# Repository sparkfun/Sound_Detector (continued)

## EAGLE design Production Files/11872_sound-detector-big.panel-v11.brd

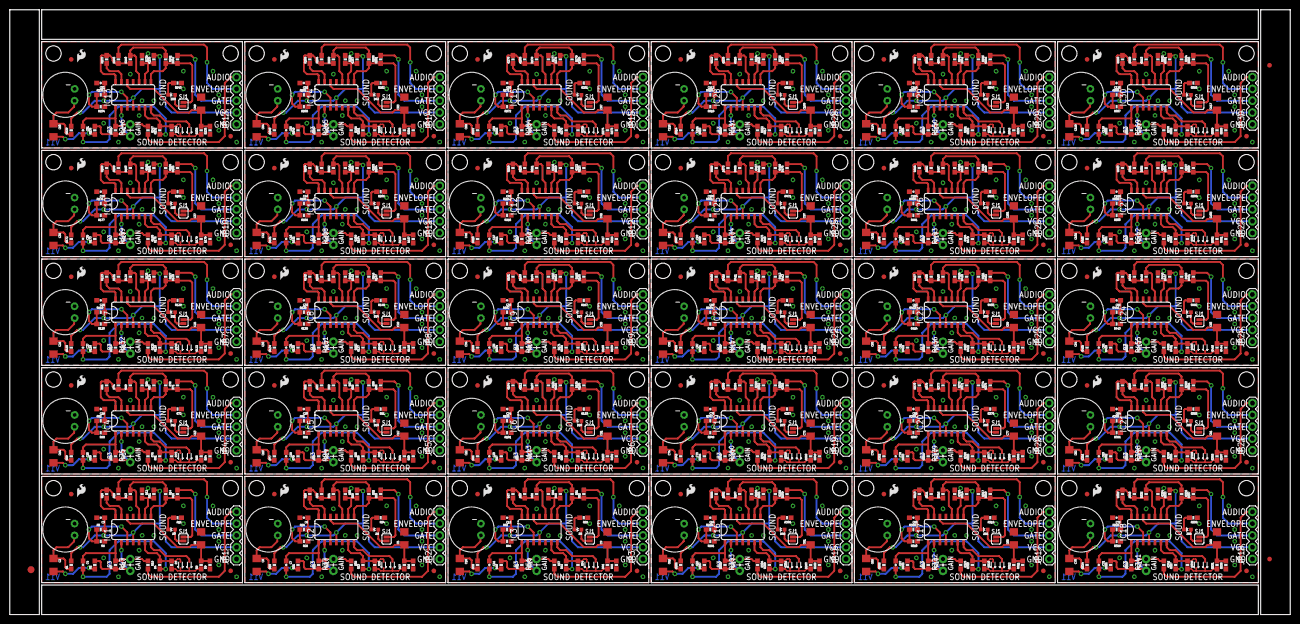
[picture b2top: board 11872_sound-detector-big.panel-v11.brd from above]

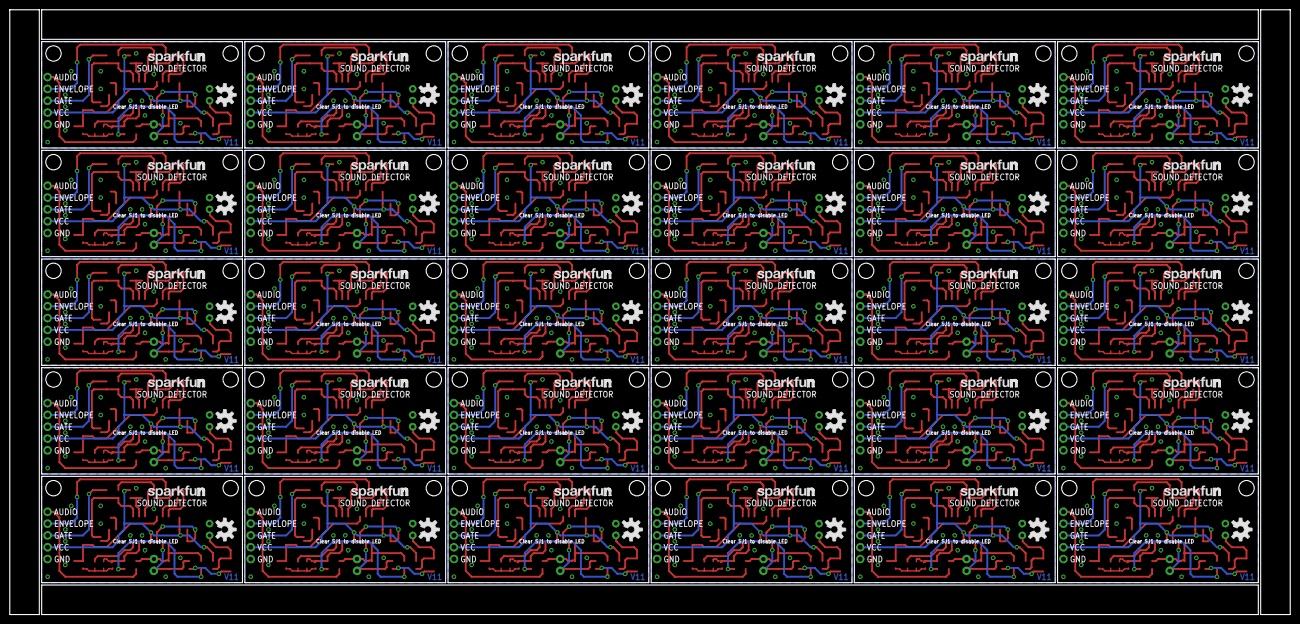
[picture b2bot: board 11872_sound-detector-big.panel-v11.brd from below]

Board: 2 copper layers, 275.3 x 130.0 mm, 1113 parts (60 on the bottom side), 660 nets.

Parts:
C1, C2, C5, C6, C9, C10, C13, C14, C17, C18, C21, C22, C25, C26, C29, C30, C33, C34, C37, C38, C41, C42, C45, C46, C49, C50, C53, C54, C57, C58, C61, C62, C65, C66, C69, C70, C73, C74, C77, C78, C81, C82, C85, C86, C89, C90, C93, C94, C97, C98, C101, C102, C105, C106, C109, C110, C113, C114, C117, C118: 10uF; 1206
C3, C4, C7, C8, C11, C12, C15, C16, C19, C20, C23, C24, C27, C28, C31, C32, C35, C36, C39, C40, C43, C44, C47, C48, C51, C52, C55, C56, C59, C60, C63, C64, C67, C68, C71, C72, C75, C76, C79, C80, C83, C84, C87, C88, C91, C92, C95, C96, C99, C100, C103, C104, C107, C108, C111, C112, C115, C116, C119, C120: 1.0uF; 0603-CAP
D1, D2, D4, D5, D7, D8, D10, D11, D13, D14, D16, D17, D19, D20, D22, D23, D25, D26, D28, D29, D31, D32, D34, D35, D37, D38, D40, D41, D43, D44, D46, D47, D49, D50, D52, D53, D55, D56, D58, D59, D61, D62, D64, D65, D67, D68, D70, D71, D73, D74, D76, D77, D79, D80, D82, D83, D85, D86, D88, D89: RB751; SOD-523
D3, D6, D9, D12, D15, D18, D21, D24, D27, D30, D33, D36, D39, D42, D45, D48, D51, D54, D57, D60, D63, D66, D69, D72, D75, D78, D81, D84, D87, D90: RED; LED-0603
E$1: FIDUCIAL-1.5X3
E$4, E$6: FIDUCIAL-1X2
FID1, FID2, FID3, FID4, FID5, FID6, FID7, FID8, FID9, FID10, FID11, FID12, FID13, FID14, FID15, FID16, FID17, FID18, FID19, FID20, FID21, FID22, FID23, FID24, FID25, FID26, FID27, FID28, FID29, FID30, FID31, FID32, FID33, FID34, FID35, FID36, FID37, FID38, FID39, FID40, FID41, FID42, FID43, FID44, FID45, FID46, FID47, FID48, FID49, FID50, FID51, FID52, FID53, FID54, FID55, FID56, FID57, FID58, FID59, FID60: FIDUCIAL1X2; FIDUCIAL-1X2
IC1, IC2, IC3, IC4, IC5, IC6, IC7, IC8, IC9, IC10, IC11, IC12, IC13, IC14, IC15, IC16, IC17, IC18, IC19, IC20, IC21, IC22, IC23, IC24, IC25, IC26, IC27, IC28, IC29, IC30: LMV324; SO014
JP1, JP2, JP3, JP4, JP5, JP6, JP7, JP8, JP9, JP10, JP11, JP12, JP13, JP14, JP15, JP16, JP17, JP18, JP19, JP20, JP21, JP22, JP23, JP24, JP25, JP26, JP27, JP28, JP29, JP30: IO Connector; 1X05
LOGO1, LOGO4, LOGO7, LOGO10, LOGO13, LOGO16, LOGO19, LOGO22, LOGO25, LOGO28, LOGO31, LOGO34, LOGO37, LOGO40, LOGO43, LOGO46, LOGO49, LOGO52, LOGO55, LOGO58, LOGO61, LOGO64, LOGO67, LOGO70, LOGO73, LOGO76, LOGO79, LOGO82, LOGO85, LOGO88: OSHW-LOGOM; OSHW-LOGO-M
LOGO2, LOGO5, LOGO8, LOGO11, LOGO14, LOGO17, LOGO20, LOGO23, LOGO26, LOGO29, LOGO32, LOGO35, LOGO38, LOGO41, LOGO44, LOGO47, LOGO50, LOGO53, LOGO56, LOGO59, LOGO62, LOGO65, LOGO68, LOGO71, LOGO74, LOGO77, LOGO80, LOGO83, LOGO86, LOGO89: LOGO-SFENW2; SFE-NEW-WEB
LOGO3, LOGO6, LOGO9, LOGO12, LOGO15, LOGO18, LOGO21, LOGO24, LOGO27, LOGO30, LOGO33, LOGO36, LOGO39, LOGO42, LOGO45, LOGO48, LOGO51, LOGO54, LOGO57, LOGO60, LOGO63, LOGO66, LOGO69, LOGO72, LOGO75, LOGO78, LOGO81, LOGO84, LOGO87, LOGO90: LOGO-SFESK; SFE-LOGO-FLAME
MIC1, MIC2, MIC3, MIC4, MIC5, MIC6, MIC7, MIC8, MIC9, MIC10, MIC11, MIC12, MIC13, MIC14, MIC15, MIC16, MIC17, MIC18, MIC19, MIC20, MIC21, MIC22, MIC23, MIC24, MIC25, MIC26, MIC27, MIC28, MIC29, MIC30: MIC9.7MM; MIC-9.7MM
R1, R16, R20, R34, R39, R53, R58, R72, R77, R91, R96, R110, R115, R129, R134, R148, R153, R167, R172, R186, R191, R205, R210, R224, R229, R243, R248, R262, R267, R281, R286, R300, R305, R319, R324, R338, R343, R357, R362, R376, R381, R395, R400, R414, R419, R433, R438, R452, R457, R471, R476, R490, R495, R509, R514, R528, R533, R547, R552, R566: 2.2k; 0603-RES
R2, R10, R13, R21, R28, R31, R40, R47, R50, R59, R66, R69, R78, R85, R88, R97, R104, R107, R116, R123, R126, R135, R142, R145, R154, R161, R164, R173, R180, R183, R192, R199, R202, R211, R218, R221, R230, R237, R240, R249, R256, R259, R268, R275, R278, R287, R294, R297, R306, R313, R316, R325, R332, R335, R344, R351, R354, R363, R370, R373, R382, R389, R392, R401, R408, R411, R420, R427, R430, R439, R446, R449, R458, R465, R468, R477, R484, R487, R496, R503, R506, R515, R522, R525, R534, R541, R544, R553, R560, R563: 1K; 0603-RES
R3, R11, R14, R22, R29, R32, R41, R48, R51, R60, R67, R70, R79, R86, R89, R98, R105, R108, R117, R124, R127, R136, R143, R146, R155, R162, R165, R174, R181, R184, R193, R200, R203, R212, R219, R222, R231, R238, R241, R250, R257, R260, R269, R276, R279, R288, R295, R298, R307, R314, R317, R326, R333, R336, R345, R352, R355, R364, R371, R374, R383, R390, R393, R402, R409, R412, R421, R428, R431, R440, R447, R450, R459, R466, R469, R478, R485, R488, R497, R504, R507, R516, R523, R526, R535, R542, R545, R554, R561, R564: 100k; 0603-RES
R4, R5, R6, R9, R23, R24, R25, R26, R42, R43, R44, R45, R61, R62, R63, R64, R80, R81, R82, R83, R99, R100, R101, R102, R118, R119, R120, R121, R137, R138, R139, R140, R156, R157, R158, R159, R175, R176, R177, R178, R194, R195, R196, R197, R213, R214, R215, R216, R232, R233, R234, R235, R251, R252, R253, R254, R270, R271, R272, R273, R289, R290, R291, R292, R308, R309, R310, R311, R327, R328, R329, R330, R346, R347, R348, R349, R365, R366, R367, R368, R384, R385, R386, R387, R403, R404, R405, R406, R422, R423, R424, R425, R441, R442, R443, R444, R460, R461, R462, R463, R479, R480, R481, R482, R498, R499, R500, R501, R517, R518, R519, R520, R536, R537, R538, R539, R555, R556, R557, R558: 10K; 0603-RES
R7, R35, R54, R73, R92, R111, R130, R149, R168, R187, R206, R225, R244, R263, R282, R301, R320, R339, R358, R377, R396, R415, R434, R453, R472, R491, R510, R529, R548, R567: 22K; 0603-RES
R8, R15, R18, R19, R27, R33, R36, R38, R46, R52, R55, R57, R65, R71, R74, R76, R84, R90, R93, R95, R103, R109, R112, R114, R122, R128, R131, R133, R141, R147, R150, R152, R160, R166, R169, R171, R179, R185, R188, R190, R198, R204, R207, R209, R217, R223, R226, R228, R236, R242, R245, R247, R255, R261, R264, R266, R274, R280, R283, R285, R293, R299, R302, R304, R312, R318, R321, R323, R331, R337, R340, R342, R350, R356, R359, R361, R369, R375, R378, R380, R388, R394, R397, R399, R407, R413, R416, R418, R426, R432, R435, R437, R445, R451, R454, R456, R464, R470, R473, R475, R483, R489, R492, R494, R502, R508, R511, R513, R521, R527, R530, R532, R540, R546, R549, R551, R559, R565, R568, R570: 100; 0603-RES
R12, R30, R49, R68, R87, R106, R125, R144, R163, R182, R201, R220, R239, R258, R277, R296, R315, R334, R353, R372, R391, R410, R429, R448, R467, R486, R505, R524, R543, R562: 3.3k; 0603-RES
R17, R37, R56, R75, R94, R113, R132, R151, R170, R189, R208, R227, R246, R265, R284, R303, R322, R341, R360, R379, R398, R417, R436, R455, R474, R493, R512, R531, R550, R569: GAIN; AXIAL-0.1EZ
SJ1, SJ2, SJ3, SJ4, SJ5, SJ6, SJ7, SJ8, SJ9, SJ10, SJ11, SJ12, SJ13, SJ14, SJ15, SJ16, SJ17, SJ18, SJ19, SJ20, SJ21, SJ22, SJ23, SJ24, SJ25, SJ26, SJ27, SJ28, SJ29, SJ30: Disable LED; SJ_2S
STANDOFF1, STANDOFF2, STANDOFF3, STANDOFF4, STANDOFF5, STANDOFF6, STANDOFF7, STANDOFF8, STANDOFF9, STANDOFF10, STANDOFF11, STANDOFF12, STANDOFF13, STANDOFF14, STANDOFF15, STANDOFF16, STANDOFF17, STANDOFF18, STANDOFF19, STANDOFF20, STANDOFF21, STANDOFF22, STANDOFF23, STANDOFF24, STANDOFF25, STANDOFF26, STANDOFF27, STANDOFF28, STANDOFF29, STANDOFF30, STANDOFF31, STANDOFF32, STANDOFF33, STANDOFF34, STANDOFF35, STANDOFF36, STANDOFF37, STANDOFF38, STANDOFF39, STANDOFF40, STANDOFF41, STANDOFF42, STANDOFF43, STANDOFF44, STANDOFF45, STANDOFF46, STANDOFF47, STANDOFF48, STANDOFF49, STANDOFF50, STANDOFF51, STANDOFF52, STANDOFF53, STANDOFF54, STANDOFF55, STANDOFF56, STANDOFF57, STANDOFF58, STANDOFF59, STANDOFF60: STAND-OFF

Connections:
AMPENV: IC1.14, R10.2, R13.1, R18.1
AMPENV1: IC2.14, R28.2, R31.1, R36.1
AMPENV2: IC3.14, R47.2, R50.1, R55.1
AMPENV3: IC4.14, R66.2, R69.1, R74.1
AMPENV4: IC5.14, R85.2, R88.1, R93.1
AMPENV5: IC6.14, R104.2, R107.1, R112.1
AMPENV6: IC7.14, R123.2, R126.1, R131.1
AMPENV7: IC8.14, R142.2, R145.1, R150.1
AMPENV8: IC9.14, R161.2, R164.1, R169.1
AMPENV9: IC10.14, R180.2, R183.1, R188.1
AMPENV10: IC11.14, R199.2, R202.1, R207.1
AMPENV11: IC12.14, R218.2, R221.1, R226.1
AMPENV12: IC13.14, R237.2, R240.1, R245.1
AMPENV13: IC14.14, R256.2, R259.1, R264.1
AMPENV14: IC15.14, R275.2, R278.1, R283.1
AMPENV15: IC16.14, R294.2, R297.1, R302.1
AMPENV16: IC17.14, R313.2, R316.1, R321.1
AMPENV17: IC18.14, R332.2, R335.1, R340.1
AMPENV18: IC19.14, R351.2, R354.1, R359.1
AMPENV19: IC20.14, R370.2, R373.1, R378.1
AMPENV20: IC21.14, R389.2, R392.1, R397.1
AMPENV21: IC22.14, R408.2, R411.1, R416.1
AMPENV22: IC23.14, R427.2, R430.1, R435.1
AMPENV23: IC24.14, R446.2, R449.1, R454.1
AMPENV24: IC25.14, R465.2, R468.1, R473.1
AMPENV25: IC26.14, R484.2, R487.1, R492.1
AMPENV26: IC27.14, R503.2, R506.1, R511.1
AMPENV27: IC28.14, R522.2, R525.1, R530.1
AMPENV28: IC29.14, R541.2, R544.1, R549.1
AMPENV29: IC30.14, R560.2, R563.1, R568.1
AUDIO: JP1.5, R19.2
AUDIO1: JP2.5, R38.2
AUDIO2: JP3.5, R57.2
AUDIO3: JP4.5, R76.2
AUDIO4: JP5.5, R95.2
AUDIO5: JP6.5, R114.2
AUDIO6: JP7.5, R133.2
AUDIO7: JP8.5, R152.2
AUDIO8: JP9.5, R171.2
AUDIO9: JP10.5, R190.2
AUDIO10: JP11.5, R209.2
AUDIO11: JP12.5, R228.2
AUDIO12: JP13.5, R247.2
AUDIO13: JP14.5, R266.2
AUDIO14: JP15.5, R285.2
AUDIO15: JP16.5, R304.2
AUDIO16: JP17.5, R323.2
AUDIO17: JP18.5, R342.2
AUDIO18: JP19.5, R361.2
AUDIO19: JP20.5, R380.2
AUDIO20: JP21.5, R399.2
AUDIO21: JP22.5, R418.2
AUDIO22: JP23.5, R437.2
AUDIO23: JP24.5, R456.2
AUDIO24: JP25.5, R475.2
AUDIO25: JP26.5, R494.2
AUDIO26: JP27.5, R513.2
AUDIO27: JP28.5, R532.2
AUDIO28: JP29.5, R551.2
AUDIO29: JP30.5, R570.2
ENVELOPE: JP1.4, R18.2
ENVELOPE1: JP2.4, R36.2
ENVELOPE2: JP3.4, R55.2
ENVELOPE3: JP4.4, R74.2
ENVELOPE4: JP5.4, R93.2
ENVELOPE5: JP6.4, R112.2
ENVELOPE6: JP7.4, R131.2
ENVELOPE7: JP8.4, R150.2
ENVELOPE8: JP9.4, R169.2
ENVELOPE9: JP10.4, R188.2
ENVELOPE10: JP11.4, R207.2
ENVELOPE11: JP12.4, R226.2
ENVELOPE12: JP13.4, R245.2
ENVELOPE13: JP14.4, R264.2
ENVELOPE14: JP15.4, R283.2
ENVELOPE15: JP16.4, R302.2
ENVELOPE16: JP17.4, R321.2
ENVELOPE17: JP18.4, R340.2
ENVELOPE18: JP19.4, R359.2
ENVELOPE19: JP20.4, R378.2
ENVELOPE20: JP21.4, R397.2
ENVELOPE21: JP22.4, R416.2
ENVELOPE22: JP23.4, R435.2
ENVELOPE23: JP24.4, R454.2
ENVELOPE24: JP25.4, R473.2
ENVELOPE25: JP26.4, R492.2
ENVELOPE26: JP27.4, R511.2
ENVELOPE27: JP28.4, R530.2
ENVELOPE28: JP29.4, R549.2
ENVELOPE29: JP30.4, R568.2
GATE: JP1.3, R15.2
GATE1: JP2.3, R33.2
GATE2: JP3.3, R52.2
GATE3: JP4.3, R71.2
GATE4: JP5.3, R90.2
GATE5: JP6.3, R109.2
GATE6: JP7.3, R128.2
GATE7: JP8.3, R147.2
GATE8: JP9.3, R166.2
GATE9: JP10.3, R185.2
GATE10: JP11.3, R204.2
GATE11: JP12.3, R223.2
GATE12: JP13.3, R242.2
GATE13: JP14.3, R261.2
GATE14: JP15.3, R280.2
GATE15: JP16.3, R299.2
GATE16: JP17.3, R318.2
GATE17: JP18.3, R337.2
GATE18: JP19.3, R356.2
GATE19: JP20.3, R375.2
GATE20: JP21.3, R394.2
GATE21: JP22.3, R413.2
GATE22: JP23.3, R432.2
GATE23: JP24.3, R451.2
GATE24: JP25.3, R470.2
GATE25: JP26.3, R489.2
GATE26: JP27.3, R508.2
GATE27: JP28.3, R527.2
GATE28: JP29.3, R546.2
GATE29: JP30.3, R565.2
GND: C1.2, C3.2, IC1.5, IC1.11, JP1.1, MIC1.2, R6.1, R9.1, R12.1, R16.1
GND1: C5.2, C8.2, IC2.5, IC2.11, JP2.1, MIC2.2, R25.1, R26.1, R30.1, R34.1
GND2: C9.2, C12.2, IC3.5, IC3.11, JP3.1, MIC3.2, R44.1, R45.1, R49.1, R53.1
GND3: C13.2, C16.2, IC4.5, IC4.11, JP4.1, MIC4.2, R63.1, R64.1, R68.1, R72.1
GND4: C17.2, C20.2, IC5.5, IC5.11, JP5.1, MIC5.2, R82.1, R83.1, R87.1, R91.1
GND5: C21.2, C24.2, IC6.5, IC6.11, JP6.1, MIC6.2, R101.1, R102.1, R106.1, R110.1
GND6: C25.2, C28.2, IC7.5, IC7.11, JP7.1, MIC7.2, R120.1, R121.1, R125.1, R129.1
GND7: C29.2, C32.2, IC8.5, IC8.11, JP8.1, MIC8.2, R139.1, R140.1, R144.1, R148.1
GND8: C33.2, C36.2, IC9.5, IC9.11, JP9.1, MIC9.2, R158.1, R159.1, R163.1, R167.1
GND9: C37.2, C40.2, IC10.5, IC10.11, JP10.1, MIC10.2, R177.1, R178.1, R182.1, R186.1
GND10: C41.2, C44.2, IC11.5, IC11.11, JP11.1, MIC11.2, R196.1, R197.1, R201.1, R205.1
GND11: C45.2, C48.2, IC12.5, IC12.11, JP12.1, MIC12.2, R215.1, R216.1, R220.1, R224.1
GND12: C49.2, C52.2, IC13.5, IC13.11, JP13.1, MIC13.2, R234.1, R235.1, R239.1, R243.1
GND13: C53.2, C56.2, IC14.5, IC14.11, JP14.1, MIC14.2, R253.1, R254.1, R258.1, R262.1
GND14: C57.2, C60.2, IC15.5, IC15.11, JP15.1, MIC15.2, R272.1, R273.1, R277.1, R281.1
GND15: C61.2, C64.2, IC16.5, IC16.11, JP16.1, MIC16.2, R291.1, R292.1, R296.1, R300.1
GND16: C65.2, C68.2, IC17.5, IC17.11, JP17.1, MIC17.2, R310.1, R311.1, R315.1, R319.1
GND17: C69.2, C72.2, IC18.5, IC18.11, JP18.1, MIC18.2, R329.1, R330.1, R334.1, R338.1
GND18: C73.2, C76.2, IC19.5, IC19.11, JP19.1, MIC19.2, R348.1, R349.1, R353.1, R357.1
GND19: C77.2, C80.2, IC20.5, IC20.11, JP20.1, MIC20.2, R367.1, R368.1, R372.1, R376.1
GND20: C81.2, C84.2, IC21.5, IC21.11, JP21.1, MIC21.2, R386.1, R387.1, R391.1, R395.1
GND21: C85.2, C88.2, IC22.5, IC22.11, JP22.1, MIC22.2, R405.1, R406.1, R410.1, R414.1
GND22: C89.2, C92.2, IC23.5, IC23.11, JP23.1, MIC23.2, R424.1, R425.1, R429.1, R433.1
GND23: C93.2, C96.2, IC24.5, IC24.11, JP24.1, MIC24.2, R443.1, R444.1, R448.1, R452.1
GND24: C97.2, C100.2, IC25.5, IC25.11, JP25.1, MIC25.2, R462.1, R463.1, R467.1, R471.1
GND25: C101.2, C104.2, IC26.5, IC26.11, JP26.1, MIC26.2, R481.1, R482.1, R486.1, R490.1
GND26: C105.2, C108.2, IC27.5, IC27.11, JP27.1, MIC27.2, R500.1, R501.1, R505.1, R509.1
GND27: C109.2, C112.2, IC28.5, IC28.11, JP28.1, MIC28.2, R519.1, R520.1, R524.1, R528.1
GND28: C113.2, C116.2, IC29.5, IC29.11, JP29.1, MIC29.2, R538.1, R539.1, R543.1, R547.1
GND29: C117.2, C120.2, IC30.5, IC30.11, JP30.1, MIC30.2, R557.1, R558.1, R562.1, R566.1
N$: C4.1, IC1.1, R3.2, R17.P$2, R19.1
unnamed: C2.1, MIC1.1, R1.1
unnamed: IC1.3, R5.1, R6.2
unnamed: D3.C, R16.2
unnamed: IC1.2, R2.2, R3.1, R17.P$1
unnamed: C2.2, R2.1
unnamed: C4.2, R4.1
unnamed: D1.A, IC1.6, R4.2, R7.1
unnamed: D2.A, IC1.7
unnamed: D1.C, D2.C, R7.2, R8.1
unnamed: C1.1, IC1.12, R8.2, R9.2
unnamed: IC1.13, R10.1
unnamed: D3.A, SJ1.1
unnamed: C6.1, MIC2.1, R20.1
unnamed: IC2.3, R24.1, R25.2
unnamed: IC1.9, R11.1, R12.2
unnamed: IC1.10, R13.2, R14.1
unnamed: IC1.8, R14.2, R15.1, SJ1.2
unnamed: IC2.2, R21.2, R22.1, R37.P$1
unnamed: C6.2, R21.1
unnamed: C7.2, R23.1
unnamed: D4.A, IC2.6, R23.2, R35.1
unnamed: D5.A, IC2.7
unnamed: D4.C, D5.C, R27.1, R35.2
unnamed: C5.1, IC2.12, R26.2, R27.2
unnamed: IC2.13, R28.1
unnamed: IC2.9, R29.1, R30.2
unnamed: IC2.10, R31.2, R32.1
unnamed: IC2.8, R32.2, R33.1, SJ2.2
unnamed: D6.C, R34.2
unnamed: D6.A, SJ2.1
unnamed: C7.1, IC2.1, R22.2, R37.P$2, R38.1
unnamed: C10.1, MIC3.1, R39.1
unnamed: IC3.3, R43.1, R44.2
unnamed: IC3.2, R40.2, R41.1, R56.P$1
unnamed: C10.2, R40.1
unnamed: C11.2, R42.1
unnamed: D7.A, IC3.6, R42.2, R54.1
unnamed: D8.A, IC3.7
unnamed: D7.C, D8.C, R46.1, R54.2
unnamed: C9.1, IC3.12, R45.2, R46.2
unnamed: IC3.13, R47.1
unnamed: IC3.9, R48.1, R49.2
unnamed: IC3.10, R50.2, R51.1
unnamed: IC3.8, R51.2, R52.1, SJ3.2
unnamed: D9.C, R53.2
unnamed: D9.A, SJ3.1
unnamed: C11.1, IC3.1, R41.2, R56.P$2, R57.1
unnamed: C14.1, MIC4.1, R58.1
unnamed: IC4.3, R62.1, R63.2
unnamed: IC4.2, R59.2, R60.1, R75.P$1
unnamed: C14.2, R59.1
unnamed: C15.2, R61.1
unnamed: D10.A, IC4.6, R61.2, R73.1
unnamed: D11.A, IC4.7
unnamed: D10.C, D11.C, R65.1, R73.2
unnamed: C13.1, IC4.12, R64.2, R65.2
unnamed: IC4.13, R66.1
unnamed: IC4.9, R67.1, R68.2
unnamed: IC4.10, R69.2, R70.1
unnamed: IC4.8, R70.2, R71.1, SJ4.2
unnamed: D12.C, R72.2
unnamed: D12.A, SJ4.1
unnamed: C15.1, IC4.1, R60.2, R75.P$2, R76.1
unnamed: C18.1, MIC5.1, R77.1
unnamed: IC5.3, R81.1, R82.2
unnamed: IC5.2, R78.2, R79.1, R94.P$1
unnamed: C18.2, R78.1
unnamed: C19.2, R80.1
unnamed: D13.A, IC5.6, R80.2, R92.1
unnamed: D14.A, IC5.7
unnamed: D13.C, D14.C, R84.1, R92.2
unnamed: C17.1, IC5.12, R83.2, R84.2
unnamed: IC5.13, R85.1
unnamed: IC5.9, R86.1, R87.2
unnamed: IC5.10, R88.2, R89.1
unnamed: IC5.8, R89.2, R90.1, SJ5.2
unnamed: D15.C, R91.2
unnamed: D15.A, SJ5.1
unnamed: C19.1, IC5.1, R79.2, R94.P$2, R95.1
unnamed: C22.1, MIC6.1, R96.1
unnamed: IC6.3, R100.1, R101.2
unnamed: IC6.2, R97.2, R98.1, R113.P$1
unnamed: C22.2, R97.1
unnamed: C23.2, R99.1
unnamed: D16.A, IC6.6, R99.2, R111.1
unnamed: D17.A, IC6.7
unnamed: D16.C, D17.C, R103.1, R111.2
unnamed: C21.1, IC6.12, R102.2, R103.2
unnamed: IC6.13, R104.1
unnamed: IC6.9, R105.1, R106.2
unnamed: IC6.10, R107.2, R108.1
unnamed: IC6.8, R108.2, R109.1, SJ6.2
unnamed: D18.C, R110.2
unnamed: D18.A, SJ6.1
unnamed: C23.1, IC6.1, R98.2, R113.P$2, R114.1
unnamed: C26.1, MIC7.1, R115.1
unnamed: IC7.3, R119.1, R120.2
unnamed: IC7.2, R116.2, R117.1, R132.P$1
unnamed: C26.2, R116.1
unnamed: C27.2, R118.1
unnamed: D19.A, IC7.6, R118.2, R130.1
unnamed: D20.A, IC7.7
unnamed: D19.C, D20.C, R122.1, R130.2
unnamed: C25.1, IC7.12, R121.2, R122.2
unnamed: IC7.13, R123.1
unnamed: IC7.9, R124.1, R125.2
unnamed: IC7.10, R126.2, R127.1
unnamed: IC7.8, R127.2, R128.1, SJ7.2
unnamed: D21.C, R129.2
unnamed: D21.A, SJ7.1
unnamed: C27.1, IC7.1, R117.2, R132.P$2, R133.1
unnamed: C30.1, MIC8.1, R134.1
unnamed: IC8.3, R138.1, R139.2
unnamed: IC8.2, R135.2, R136.1, R151.P$1
unnamed: C30.2, R135.1
unnamed: C31.2, R137.1
unnamed: D22.A, IC8.6, R137.2, R149.1
unnamed: D23.A, IC8.7
unnamed: D22.C, D23.C, R141.1, R149.2
unnamed: C29.1, IC8.12, R140.2, R141.2
unnamed: IC8.13, R142.1
unnamed: IC8.9, R143.1, R144.2
unnamed: IC8.10, R145.2, R146.1
unnamed: IC8.8, R146.2, R147.1, SJ8.2
unnamed: D24.C, R148.2
unnamed: D24.A, SJ8.1
unnamed: C31.1, IC8.1, R136.2, R151.P$2, R152.1
unnamed: C34.1, MIC9.1, R153.1
unnamed: IC9.3, R157.1, R158.2
unnamed: IC9.2, R154.2, R155.1, R170.P$1
unnamed: C34.2, R154.1
unnamed: C35.2, R156.1
unnamed: D25.A, IC9.6, R156.2, R168.1
unnamed: D26.A, IC9.7
unnamed: D25.C, D26.C, R160.1, R168.2
unnamed: C33.1, IC9.12, R159.2, R160.2
unnamed: IC9.13, R161.1
unnamed: IC9.9, R162.1, R163.2
unnamed: IC9.10, R164.2, R165.1
unnamed: IC9.8, R165.2, R166.1, SJ9.2
unnamed: D27.C, R167.2
unnamed: D27.A, SJ9.1
unnamed: C35.1, IC9.1, R155.2, R170.P$2, R171.1
unnamed: C38.1, MIC10.1, R172.1
unnamed: IC10.3, R176.1, R177.2
unnamed: IC10.2, R173.2, R174.1, R189.P$1
unnamed: C38.2, R173.1
unnamed: C39.2, R175.1
unnamed: D28.A, IC10.6, R175.2, R187.1
unnamed: D29.A, IC10.7
unnamed: D28.C, D29.C, R179.1, R187.2
unnamed: C37.1, IC10.12, R178.2, R179.2
unnamed: IC10.13, R180.1
unnamed: IC10.9, R181.1, R182.2
unnamed: IC10.10, R183.2, R184.1
unnamed: IC10.8, R184.2, R185.1, SJ10.2
unnamed: D30.C, R186.2
unnamed: D30.A, SJ10.1
unnamed: C39.1, IC10.1, R174.2, R189.P$2, R190.1
unnamed: C42.1, MIC11.1, R191.1
unnamed: IC11.3, R195.1, R196.2
unnamed: IC11.2, R192.2, R193.1, R208.P$1
unnamed: C42.2, R192.1
unnamed: C43.2, R194.1
unnamed: D31.A, IC11.6, R194.2, R206.1
unnamed: D32.A, IC11.7
unnamed: D31.C, D32.C, R198.1, R206.2
unnamed: C41.1, IC11.12, R197.2, R198.2
unnamed: IC11.13, R199.1
unnamed: IC11.9, R200.1, R201.2
unnamed: IC11.10, R202.2, R203.1
unnamed: IC11.8, R203.2, R204.1, SJ11.2
unnamed: D33.C, R205.2
unnamed: D33.A, SJ11.1
unnamed: C43.1, IC11.1, R193.2, R208.P$2, R209.1
unnamed: C46.1, MIC12.1, R210.1
unnamed: IC12.3, R214.1, R215.2
unnamed: IC12.2, R211.2, R212.1, R227.P$1
unnamed: C46.2, R211.1
unnamed: C47.2, R213.1
unnamed: D34.A, IC12.6, R213.2, R225.1
unnamed: D35.A, IC12.7
unnamed: D34.C, D35.C, R217.1, R225.2
unnamed: C45.1, IC12.12, R216.2, R217.2
unnamed: IC12.13, R218.1
unnamed: IC12.9, R219.1, R220.2
unnamed: IC12.10, R221.2, R222.1
unnamed: IC12.8, R222.2, R223.1, SJ12.2
unnamed: D36.C, R224.2
unnamed: D36.A, SJ12.1
unnamed: C47.1, IC12.1, R212.2, R227.P$2, R228.1
unnamed: C50.1, MIC13.1, R229.1
unnamed: IC13.3, R233.1, R234.2
unnamed: IC13.2, R230.2, R231.1, R246.P$1
unnamed: C50.2, R230.1
unnamed: C51.2, R232.1
unnamed: D37.A, IC13.6, R232.2, R244.1
unnamed: D38.A, IC13.7
unnamed: D37.C, D38.C, R236.1, R244.2
unnamed: C49.1, IC13.12, R235.2, R236.2
unnamed: IC13.13, R237.1
unnamed: IC13.9, R238.1, R239.2
unnamed: IC13.10, R240.2, R241.1
unnamed: IC13.8, R241.2, R242.1, SJ13.2
unnamed: D39.C, R243.2
unnamed: D39.A, SJ13.1
unnamed: C51.1, IC13.1, R231.2, R246.P$2, R247.1
unnamed: C54.1, MIC14.1, R248.1
unnamed: IC14.3, R252.1, R253.2
unnamed: IC14.2, R249.2, R250.1, R265.P$1
unnamed: C54.2, R249.1
unnamed: C55.2, R251.1
unnamed: D40.A, IC14.6, R251.2, R263.1
unnamed: D41.A, IC14.7
unnamed: D40.C, D41.C, R255.1, R263.2
unnamed: C53.1, IC14.12, R254.2, R255.2
unnamed: IC14.13, R256.1
unnamed: IC14.9, R257.1, R258.2
unnamed: IC14.10, R259.2, R260.1
unnamed: IC14.8, R260.2, R261.1, SJ14.2
unnamed: D42.C, R262.2
unnamed: D42.A, SJ14.1
unnamed: C55.1, IC14.1, R250.2, R265.P$2, R266.1
unnamed: C58.1, MIC15.1, R267.1
unnamed: IC15.3, R271.1, R272.2
unnamed: IC15.2, R268.2, R269.1, R284.P$1
unnamed: C58.2, R268.1
unnamed: C59.2, R270.1
unnamed: D43.A, IC15.6, R270.2, R282.1
unnamed: D44.A, IC15.7
unnamed: D43.C, D44.C, R274.1, R282.2
unnamed: C57.1, IC15.12, R273.2, R274.2
unnamed: IC15.13, R275.1
unnamed: IC15.9, R276.1, R277.2
unnamed: IC15.10, R278.2, R279.1
unnamed: IC15.8, R279.2, R280.1, SJ15.2
unnamed: D45.C, R281.2
unnamed: D45.A, SJ15.1
unnamed: C59.1, IC15.1, R269.2, R284.P$2, R285.1
unnamed: C62.1, MIC16.1, R286.1
unnamed: IC16.3, R290.1, R291.2
unnamed: IC16.2, R287.2, R288.1, R303.P$1
unnamed: C62.2, R287.1
unnamed: C63.2, R289.1
unnamed: D46.A, IC16.6, R289.2, R301.1
unnamed: D47.A, IC16.7
unnamed: D46.C, D47.C, R293.1, R301.2
unnamed: C61.1, IC16.12, R292.2, R293.2
unnamed: IC16.13, R294.1
unnamed: IC16.9, R295.1, R296.2
unnamed: IC16.10, R297.2, R298.1
unnamed: IC16.8, R298.2, R299.1, SJ16.2
unnamed: D48.C, R300.2
unnamed: D48.A, SJ16.1
unnamed: C63.1, IC16.1, R288.2, R303.P$2, R304.1
unnamed: C66.1, MIC17.1, R305.1
unnamed: IC17.3, R309.1, R310.2
unnamed: IC17.2, R306.2, R307.1, R322.P$1
unnamed: C66.2, R306.1
unnamed: C67.2, R308.1
unnamed: D49.A, IC17.6, R308.2, R320.1
unnamed: D50.A, IC17.7
unnamed: D49.C, D50.C, R312.1, R320.2
unnamed: C65.1, IC17.12, R311.2, R312.2
unnamed: IC17.13, R313.1
unnamed: IC17.9, R314.1, R315.2
unnamed: IC17.10, R316.2, R317.1
unnamed: IC17.8, R317.2, R318.1, SJ17.2
unnamed: D51.C, R319.2
unnamed: D51.A, SJ17.1
unnamed: C67.1, IC17.1, R307.2, R322.P$2, R323.1
unnamed: C70.1, MIC18.1, R324.1
unnamed: IC18.3, R328.1, R329.2
unnamed: IC18.2, R325.2, R326.1, R341.P$1
unnamed: C70.2, R325.1
unnamed: C71.2, R327.1
unnamed: D52.A, IC18.6, R327.2, R339.1
unnamed: D53.A, IC18.7
unnamed: D52.C, D53.C, R331.1, R339.2
unnamed: C69.1, IC18.12, R330.2, R331.2
unnamed: IC18.13, R332.1
unnamed: IC18.9, R333.1, R334.2
unnamed: IC18.10, R335.2, R336.1
unnamed: IC18.8, R336.2, R337.1, SJ18.2
unnamed: D54.C, R338.2
unnamed: D54.A, SJ18.1
unnamed: C71.1, IC18.1, R326.2, R341.P$2, R342.1
unnamed: C74.1, MIC19.1, R343.1
unnamed: IC19.3, R347.1, R348.2
unnamed: IC19.2, R344.2, R345.1, R360.P$1
unnamed: C74.2, R344.1
unnamed: C75.2, R346.1
unnamed: D55.A, IC19.6, R346.2, R358.1
unnamed: D56.A, IC19.7
unnamed: D55.C, D56.C, R350.1, R358.2
unnamed: C73.1, IC19.12, R349.2, R350.2
unnamed: IC19.13, R351.1
unnamed: IC19.9, R352.1, R353.2
unnamed: IC19.10, R354.2, R355.1
unnamed: IC19.8, R355.2, R356.1, SJ19.2
unnamed: D57.C, R357.2
unnamed: D57.A, SJ19.1
unnamed: C75.1, IC19.1, R345.2, R360.P$2, R361.1
unnamed: C78.1, MIC20.1, R362.1
unnamed: IC20.3, R366.1, R367.2
unnamed: IC20.2, R363.2, R364.1, R379.P$1
unnamed: C78.2, R363.1
unnamed: C79.2, R365.1
unnamed: D58.A, IC20.6, R365.2, R377.1
unnamed: D59.A, IC20.7
unnamed: D58.C, D59.C, R369.1, R377.2
unnamed: C77.1, IC20.12, R368.2, R369.2
unnamed: IC20.13, R370.1
unnamed: IC20.9, R371.1, R372.2
unnamed: IC20.10, R373.2, R374.1
unnamed: IC20.8, R374.2, R375.1, SJ20.2
unnamed: D60.C, R376.2
unnamed: D60.A, SJ20.1
unnamed: C79.1, IC20.1, R364.2, R379.P$2, R380.1
unnamed: C82.1, MIC21.1, R381.1
unnamed: IC21.3, R385.1, R386.2
unnamed: IC21.2, R382.2, R383.1, R398.P$1
unnamed: C82.2, R382.1
unnamed: C83.2, R384.1
unnamed: D61.A, IC21.6, R384.2, R396.1
unnamed: D62.A, IC21.7
unnamed: D61.C, D62.C, R388.1, R396.2
unnamed: C81.1, IC21.12, R387.2, R388.2
unnamed: IC21.13, R389.1
unnamed: IC21.9, R390.1, R391.2
unnamed: IC21.10, R392.2, R393.1
unnamed: IC21.8, R393.2, R394.1, SJ21.2
unnamed: D63.C, R395.2
unnamed: D63.A, SJ21.1
unnamed: C83.1, IC21.1, R383.2, R398.P$2, R399.1
unnamed: C86.1, MIC22.1, R400.1
unnamed: IC22.3, R404.1, R405.2
unnamed: IC22.2, R401.2, R402.1, R417.P$1
unnamed: C86.2, R401.1
unnamed: C87.2, R403.1
unnamed: D64.A, IC22.6, R403.2, R415.1
unnamed: D65.A, IC22.7
unnamed: D64.C, D65.C, R407.1, R415.2
unnamed: C85.1, IC22.12, R406.2, R407.2
unnamed: IC22.13, R408.1
unnamed: IC22.9, R409.1, R410.2
unnamed: IC22.10, R411.2, R412.1
unnamed: IC22.8, R412.2, R413.1, SJ22.2
unnamed: D66.C, R414.2
unnamed: D66.A, SJ22.1
unnamed: C87.1, IC22.1, R402.2, R417.P$2, R418.1
unnamed: C90.1, MIC23.1, R419.1
unnamed: IC23.3, R423.1, R424.2
unnamed: IC23.2, R420.2, R421.1, R436.P$1
unnamed: C90.2, R420.1
unnamed: C91.2, R422.1
unnamed: D67.A, IC23.6, R422.2, R434.1
unnamed: D68.A, IC23.7
unnamed: D67.C, D68.C, R426.1, R434.2
unnamed: C89.1, IC23.12, R425.2, R426.2
unnamed: IC23.13, R427.1
unnamed: IC23.9, R428.1, R429.2
unnamed: IC23.10, R430.2, R431.1
unnamed: IC23.8, R431.2, R432.1, SJ23.2
unnamed: D69.C, R433.2
unnamed: D69.A, SJ23.1
unnamed: C91.1, IC23.1, R421.2, R436.P$2, R437.1
unnamed: C94.1, MIC24.1, R438.1
unnamed: IC24.3, R442.1, R443.2
unnamed: IC24.2, R439.2, R440.1, R455.P$1
unnamed: C94.2, R439.1
unnamed: C95.2, R441.1
unnamed: D70.A, IC24.6, R441.2, R453.1
unnamed: D71.A, IC24.7
unnamed: D70.C, D71.C, R445.1, R453.2
unnamed: C93.1, IC24.12, R444.2, R445.2
unnamed: IC24.13, R446.1
unnamed: IC24.9, R447.1, R448.2
unnamed: IC24.10, R449.2, R450.1
unnamed: IC24.8, R450.2, R451.1, SJ24.2
unnamed: D72.C, R452.2
unnamed: D72.A, SJ24.1
unnamed: C95.1, IC24.1, R440.2, R455.P$2, R456.1
unnamed: C98.1, MIC25.1, R457.1
unnamed: IC25.3, R461.1, R462.2
unnamed: IC25.2, R458.2, R459.1, R474.P$1
unnamed: C98.2, R458.1
unnamed: C99.2, R460.1
unnamed: D73.A, IC25.6, R460.2, R472.1
unnamed: D74.A, IC25.7
unnamed: D73.C, D74.C, R464.1, R472.2
unnamed: C97.1, IC25.12, R463.2, R464.2
unnamed: IC25.13, R465.1
unnamed: IC25.9, R466.1, R467.2
unnamed: IC25.10, R468.2, R469.1
unnamed: IC25.8, R469.2, R470.1, SJ25.2
unnamed: D75.C, R471.2
unnamed: D75.A, SJ25.1
unnamed: C99.1, IC25.1, R459.2, R474.P$2, R475.1
unnamed: C102.1, MIC26.1, R476.1
unnamed: IC26.3, R480.1, R481.2
unnamed: IC26.2, R477.2, R478.1, R493.P$1
unnamed: C102.2, R477.1
unnamed: C103.2, R479.1
unnamed: D76.A, IC26.6, R479.2, R491.1
unnamed: D77.A, IC26.7
unnamed: D76.C, D77.C, R483.1, R491.2
unnamed: C101.1, IC26.12, R482.2, R483.2
unnamed: IC26.13, R484.1
unnamed: IC26.9, R485.1, R486.2
unnamed: IC26.10, R487.2, R488.1
unnamed: IC26.8, R488.2, R489.1, SJ26.2
unnamed: D78.C, R490.2
unnamed: D78.A, SJ26.1
unnamed: C103.1, IC26.1, R478.2, R493.P$2, R494.1
unnamed: C106.1, MIC27.1, R495.1
unnamed: IC27.3, R499.1, R500.2
unnamed: IC27.2, R496.2, R497.1, R512.P$1
unnamed: C106.2, R496.1
unnamed: C107.2, R498.1
unnamed: D79.A, IC27.6, R498.2, R510.1
unnamed: D80.A, IC27.7
unnamed: D79.C, D80.C, R502.1, R510.2
unnamed: C105.1, IC27.12, R501.2, R502.2
unnamed: IC27.13, R503.1
unnamed: IC27.9, R504.1, R505.2
unnamed: IC27.10, R506.2, R507.1
unnamed: IC27.8, R507.2, R508.1, SJ27.2
unnamed: D81.C, R509.2
unnamed: D81.A, SJ27.1
unnamed: C107.1, IC27.1, R497.2, R512.P$2, R513.1
unnamed: C110.1, MIC28.1, R514.1
unnamed: IC28.3, R518.1, R519.2
unnamed: IC28.2, R515.2, R516.1, R531.P$1
unnamed: C110.2, R515.1
unnamed: C111.2, R517.1
unnamed: D82.A, IC28.6, R517.2, R529.1
unnamed: D83.A, IC28.7
unnamed: D82.C, D83.C, R521.1, R529.2
unnamed: C109.1, IC28.12, R520.2, R521.2
unnamed: IC28.13, R522.1
unnamed: IC28.9, R523.1, R524.2
unnamed: IC28.10, R525.2, R526.1
unnamed: IC28.8, R526.2, R527.1, SJ28.2
unnamed: D84.C, R528.2
unnamed: D84.A, SJ28.1
unnamed: C111.1, IC28.1, R516.2, R531.P$2, R532.1
unnamed: C114.1, MIC29.1, R533.1
unnamed: IC29.3, R537.1, R538.2
unnamed: IC29.2, R534.2, R535.1, R550.P$1
unnamed: C114.2, R534.1
unnamed: C115.2, R536.1
unnamed: D85.A, IC29.6, R536.2, R548.1
unnamed: D86.A, IC29.7
unnamed: D85.C, D86.C, R540.1, R548.2
unnamed: C113.1, IC29.12, R539.2, R540.2
unnamed: IC29.13, R541.1
unnamed: IC29.9, R542.1, R543.2
unnamed: IC29.10, R544.2, R545.1
unnamed: IC29.8, R545.2, R546.1, SJ29.2
unnamed: D87.C, R547.2
unnamed: D87.A, SJ29.1
unnamed: C115.1, IC29.1, R535.2, R550.P$2, R551.1
unnamed: C118.1, MIC30.1, R552.1
unnamed: IC30.3, R556.1, R557.2
unnamed: IC30.2, R553.2, R554.1, R569.P$1
unnamed: C118.2, R553.1
unnamed: C119.2, R555.1
unnamed: D88.A, IC30.6, R555.2, R567.1
unnamed: D89.A, IC30.7
unnamed: D88.C, D89.C, R559.1, R567.2
unnamed: C117.1, IC30.12, R558.2, R559.2
unnamed: IC30.13, R560.1
unnamed: IC30.9, R561.1, R562.2
unnamed: IC30.10, R563.2, R564.1
unnamed: IC30.8, R564.2, R565.1, SJ30.2
unnamed: D90.C, R566.2
unnamed: D90.A, SJ30.1
unnamed: C119.1, IC30.1, R554.2, R569.P$2, R570.1
VCC: C3.1, IC1.4, JP1.2, R1.2, R5.2, R11.2
VCC1: C8.1, IC2.4, JP2.2, R20.2, R24.2, R29.2
VCC2: C12.1, IC3.4, JP3.2, R39.2, R43.2, R48.2
VCC3: C16.1, IC4.4, JP4.2, R58.2, R62.2, R67.2
VCC4: C20.1, IC5.4, JP5.2, R77.2, R81.2, R86.2
VCC5: C24.1, IC6.4, JP6.2, R96.2, R100.2, R105.2
VCC6: C28.1, IC7.4, JP7.2, R115.2, R119.2, R124.2
VCC7: C32.1, IC8.4, JP8.2, R134.2, R138.2, R143.2
VCC8: C36.1, IC9.4, JP9.2, R153.2, R157.2, R162.2
VCC9: C40.1, IC10.4, JP10.2, R172.2, R176.2, R181.2
VCC10: C44.1, IC11.4, JP11.2, R191.2, R195.2, R200.2
VCC11: C48.1, IC12.4, JP12.2, R210.2, R214.2, R219.2
VCC12: C52.1, IC13.4, JP13.2, R229.2, R233.2, R238.2
VCC13: C56.1, IC14.4, JP14.2, R248.2, R252.2, R257.2
VCC14: C60.1, IC15.4, JP15.2, R267.2, R271.2, R276.2
VCC15: C64.1, IC16.4, JP16.2, R286.2, R290.2, R295.2
VCC16: C68.1, IC17.4, JP17.2, R305.2, R309.2, R314.2
VCC17: C72.1, IC18.4, JP18.2, R324.2, R328.2, R333.2
VCC18: C76.1, IC19.4, JP19.2, R343.2, R347.2, R352.2
VCC19: C80.1, IC20.4, JP20.2, R362.2, R366.2, R371.2
VCC20: C84.1, IC21.4, JP21.2, R381.2, R385.2, R390.2
VCC21: C88.1, IC22.4, JP22.2, R400.2, R404.2, R409.2
VCC22: C92.1, IC23.4, JP23.2, R419.2, R423.2, R428.2
VCC23: C96.1, IC24.4, JP24.2, R438.2, R442.2, R447.2
VCC24: C100.1, IC25.4, JP25.2, R457.2, R461.2, R466.2
VCC25: C104.1, IC26.4, JP26.2, R476.2, R480.2, R485.2
VCC26: C108.1, IC27.4, JP27.2, R495.2, R499.2, R504.2
VCC27: C112.1, IC28.4, JP28.2, R514.2, R518.2, R523.2
VCC28: C116.1, IC29.4, JP29.2, R533.2, R537.2, R542.2
VCC29: C120.1, IC30.4, JP30.2, R552.2, R556.2, R561.2

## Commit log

2013-11-14 Initial commit - gitignore and readme
2013-11-14 Initial checkin of schematic and PCB files
2013-11-14 Updating 3k3 resistor to Sparkle part.
2013-11-15 Fixed width of board outline.
2013-12-03 Changing resistor value convention.
    R12 changed from 3k3 to 3.3k.
2013-12-10 Changes based on green board review
    -All text to vector
    -fixed diode footprint to diodes.inc recommendations
    --Added legend text for gain set resistors
2013-12-16 Ready for reds
    Changed after group review:
    -net width of schem
    -Vector text
    -IC naming
    -Correct logos
    -Minor electrical cleanup
2013-12-18 Added local board fiducials and paneled
2014-02-05 Start on documentation
2014-02-20 Code and documentation
    Work in progress
2014-02-20 Forgot the firmware in last commit
    Still WIP.
2014-02-22 Updating docs and firmware
2014-02-27 Prepping for go-live
    Added Fritzing sample and cleaned things up a bit.
2014-02-28 Updating repo organization
2014-02-28 Remioving incomplete documentation.
    Please see the online hookup guide for actual docs:
    https://learn.sparkfun.com/tutorials/sound-detector-hookup-guide
2014-03-03 Fixing SJ1 silkscreen
    From Bug 8552: SJ1 had been labeled using the smash command, with the
    name moved from tNames to tPlace. Every board on the panel incremented
    it's value (SJ1, SJ2 up to SJ15).
    This makes the label on SJ1 a simple text object, which shouldn't
    increment for each instance on the panel.
2014-03-03 Rolling board rev number
    From V10 to V11
2014-03-04 changed fiducial from micro to regular
2014-03-04 Created Panel v11
    v11 has the corrected silk
2016-10-31 Fixing incorrect version number on schematic
2017-07-21 New Big Panel
